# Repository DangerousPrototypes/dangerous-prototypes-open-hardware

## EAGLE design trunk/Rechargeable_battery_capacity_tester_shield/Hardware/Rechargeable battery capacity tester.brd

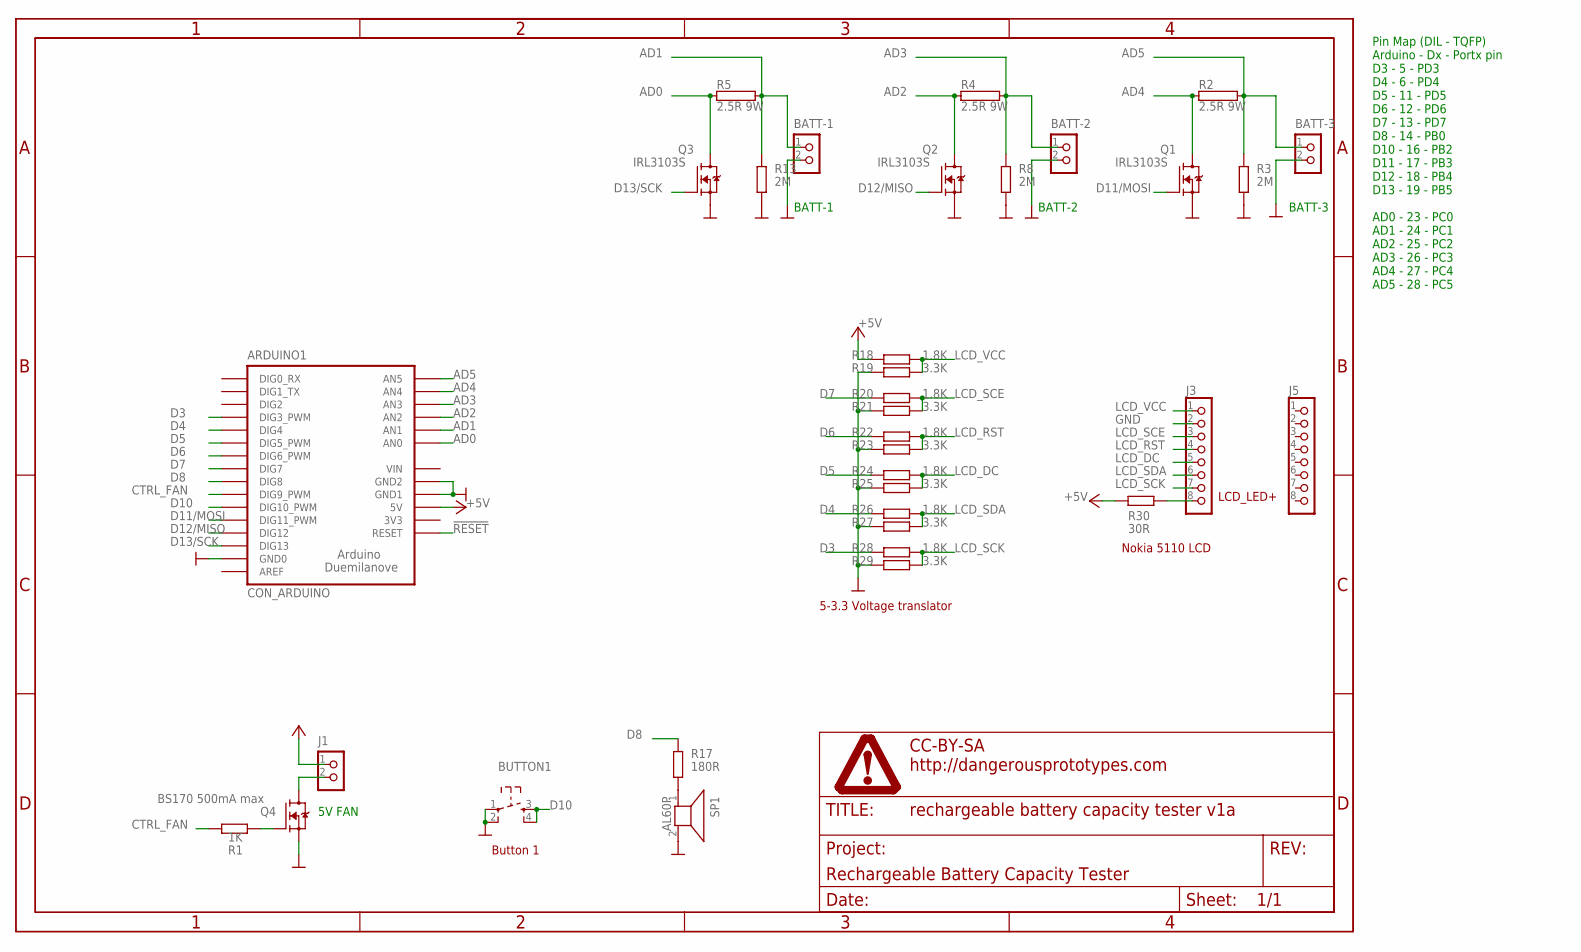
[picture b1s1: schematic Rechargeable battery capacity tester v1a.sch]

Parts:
ARDUINO1: CON_ARDUINO
BATT-1, BATT-2, BATT-3: CON_TERMINAL_BLOCK_02-5MM; TERMINAL_BLOCK_2P_5
BUTTON1: SW_TACT_4P; SW_TACT_SMALL
J1: CON_JST_2PIN-PTH; CON_JST_2PIN
J3, J5: CON_HEADER_1X08-PTH; M1X8
Q1, Q2, Q3: IRL3103S; D2PAK
Q4: BS170 500mA max; SOT-23
R1: 1K; R603
R2, R4, R5: 2.5R 9W; KH214-8
R3, R8, R13: 2M; R603
R17: 180R; R603
R18, R20, R22, R24, R26, R28: 1.8K; R603
R19, R21, R23, R25, R27, R29: 3.3K; R603
R30: 30R; R603
SP1: AL60P
U$1: FRAME_DINA4_L; DP_LOGO

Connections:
!RESET: ARDUINO1.RESET
+5V: ARDUINO1.5V, J1.1, R18.1, R30.1
AD0: ARDUINO1.A_0 (AN0), Q3.2 (D), R5.1
AD1: ARDUINO1.A_1 (AN1), BATT-1.1, R5.2, R13.2
AD2: ARDUINO1.A_2 (AN2), Q2.2 (D), R4.1
AD3: ARDUINO1.A_3 (AN3), BATT-2.1, R4.2, R8.2
AD4: ARDUINO1.A_4 (AN4), Q1.2 (D), R2.1
AD5: ARDUINO1.A_5 (AN5), BATT-3.1, R2.2, R3.2
D3: ARDUINO1.D_3 (DIG3_PWM), R28.1
D4: ARDUINO1.D_4 (DIG4), R26.1
D5: ARDUINO1.D_5 (DIG5_PWM), R24.1
D6: ARDUINO1.D_6 (DIG6_PWM), R22.1
D7: ARDUINO1.D_7 (DIG7), R20.1
D8: ARDUINO1.D_8 (DIG8), R17.2
D10: ARDUINO1.D_10 (DIG10_PWM), BUTTON1.3, BUTTON1.4
D11/MOSI: ARDUINO1.D_11 (DIG11_PWM), Q1.1 (G)
D12/MISO: ARDUINO1.D_12 (DIG12), Q2.1 (G)
D13/SCK: ARDUINO1.D_13 (DIG13), Q3.1 (G)
GND: ARDUINO1.GND0, ARDUINO1.GND1, ARDUINO1.GND2, BATT-1.2, BATT-2.2, BATT-3.2, BUTTON1.1, BUTTON1.2, J3.2, Q1.3 (S), Q2.3 (S), Q3.3 (S), Q4.2 (S), R3.1, R8.1, R13.1, R19.1, R21.1, R23.1, R25.1, R27.1, R29.1, SP1.2
LCD_DC: J3.5, R24.2, R25.2
LCD_RST: J3.4, R22.2, R23.2
LCD_SCE: J3.3, R20.2, R21.2
LCD_SCK: J3.7, R28.2, R29.2
LCD_SDA: J3.6, R26.2, R27.2
LCD_VCC: J3.1, R18.2, R19.2
unnamed: J3.8, R30.2
unnamed: R17.1, SP1.1
unnamed: J1.2, Q4.3 (D)
unnamed: Q4.1 (G), R1.2
unnamed: ARDUINO1.D_9 (DIG9_PWM), R1.1
VIN: ARDUINO1.VIN

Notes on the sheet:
Pin Map (DIL - TQFP) Arduino - Dx - Portx pin D3 - 5 - PD3 D4 - 6 - PD4 D5 - 11 - PD5 D6 - 12 - PD6 D7 - 13 - PD7 D8 - 14 - PB0 D10 - 16 - PB2 D11 - 17 - PB3 D12 - 18 - PB4 D13 - 19 - PB5 AD0 - 23 - PC0 AD1 - 24 - PC1 AD2 - 25 - PC2 AD3 - 26 - PC3 AD4 - 27 - PC4 AD5 - 28 - PC5
BATT-3
BATT-2
BATT-1
Button 1
LCD_LED+
Nokia 5110 LCD
5-3.3 Voltage translator
5V FAN

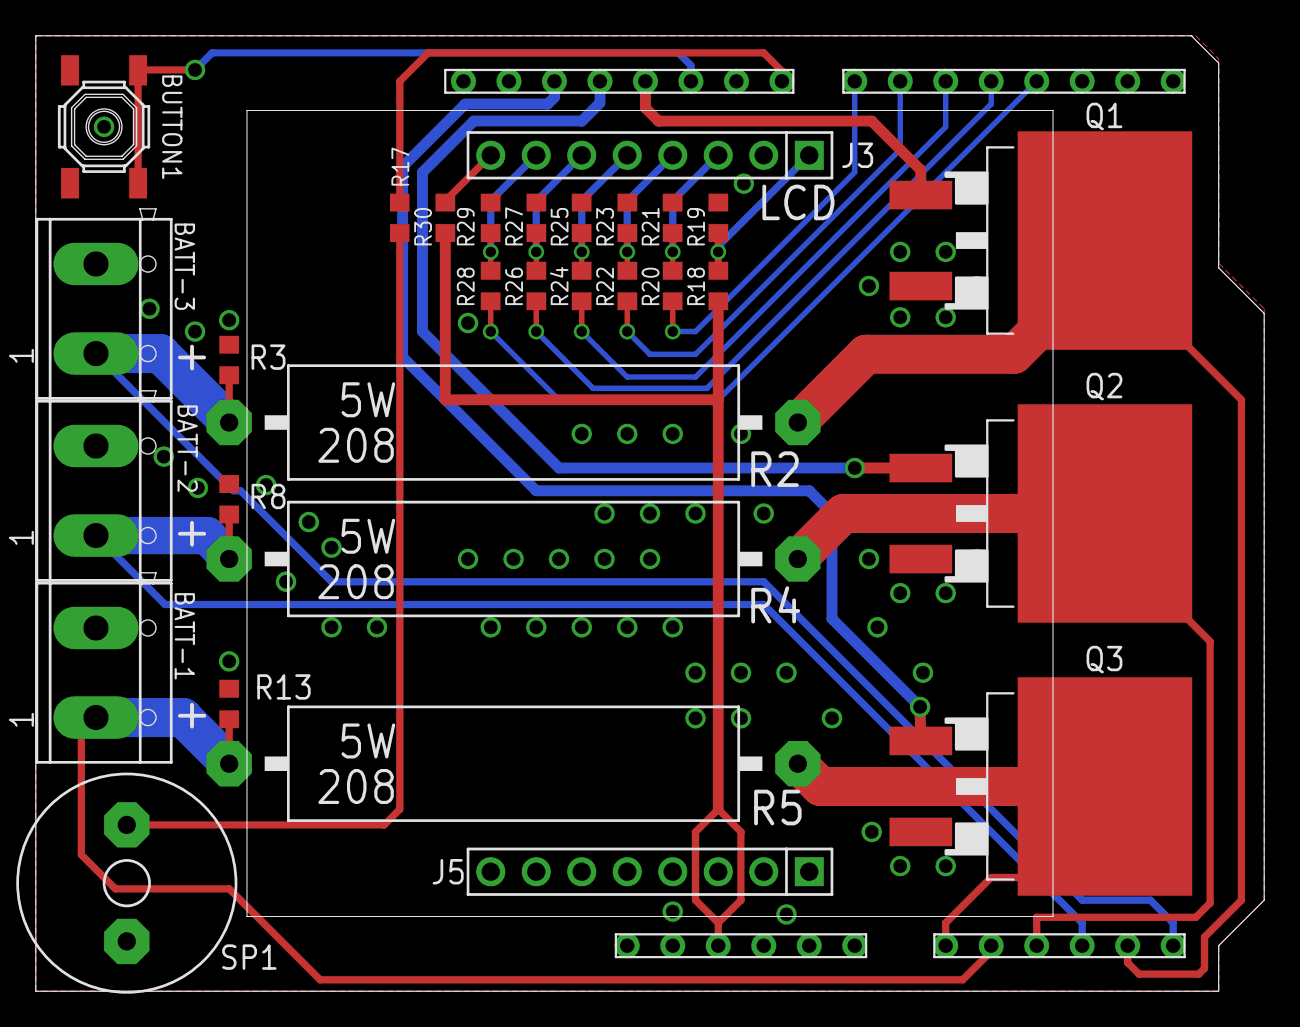
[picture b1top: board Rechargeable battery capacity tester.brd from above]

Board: 2 copper layers, 68.6 x 53.3 mm, 33 parts (1 on the bottom side), 26 nets.

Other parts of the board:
U$2: DP_LOGO_ART_1X1

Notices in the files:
trunk/Rechargeable_battery_capacity_tester_shield/Hardware/Rechargeable battery capacity tester.brd:
LICENSE: CC-BY-SA
